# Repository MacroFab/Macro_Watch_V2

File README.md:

***
### Macro_Watch_V2
***
**Low cost, binary watch based off the Silicon Labs EFM8SB10F2G-A-QFN20R MCU for promotional purposes at MacroFab, INC.**

This repository contains all the documentation and instructions needed to build a Macro_Watch. The Macro_Watch is designed to be mounted on an ESD wrist band. It is designed to be programmed with the [Silicon Labs USB Debug Adapter](http://www.silabs.com/products/mcu/Pages/USBDebug.aspx) and the [SiLabs2TC](https://github.com/MacroFab/Macro_Articles/tree/master/SiLabs2TC) board. 

Check the [MacroFab, INC. Engineering Blog](https://macrofab.com/blog/engineering/) for more information.

***
**License Information**

This project is under the [Creative Commons Attribution-ShareAlike 4.0 International License](LICENSE.md). This project is provided with no warranty and should be used at your own risk. 

***
**Board Layout**

***
**Board Schematic**

***
**Completed Macro_Watch V2**

***
**Macro_Watch V2 being programmed**

***
**Directory listing of the repository**

| Directory | Description |
|---|---|
| Hardware | Contains all the hardware files for the Macro_Watch. Designed with Eagle V6.0+. | 
| Software | Has all the firmware that needs to be loaded onto the Macro_Watch. Written in C for Simplicity Studio. |

***
**Credits**

Designed by:   
Parker Dillmann  

Software by:   
Parker Dillmann  

***

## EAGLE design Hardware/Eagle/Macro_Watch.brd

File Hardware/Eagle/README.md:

###Macro_Watch Hardware
***
**Low cost, binary watch based off the Silicon Labs EFM8SB10F2G-A-QFN20R MCU for promotional purposes at MacroFab, INC.**

***

***

***

Files are for Eagle V6.0+. Gerber files can be found in the camfiles directory. See main directory for licensing.

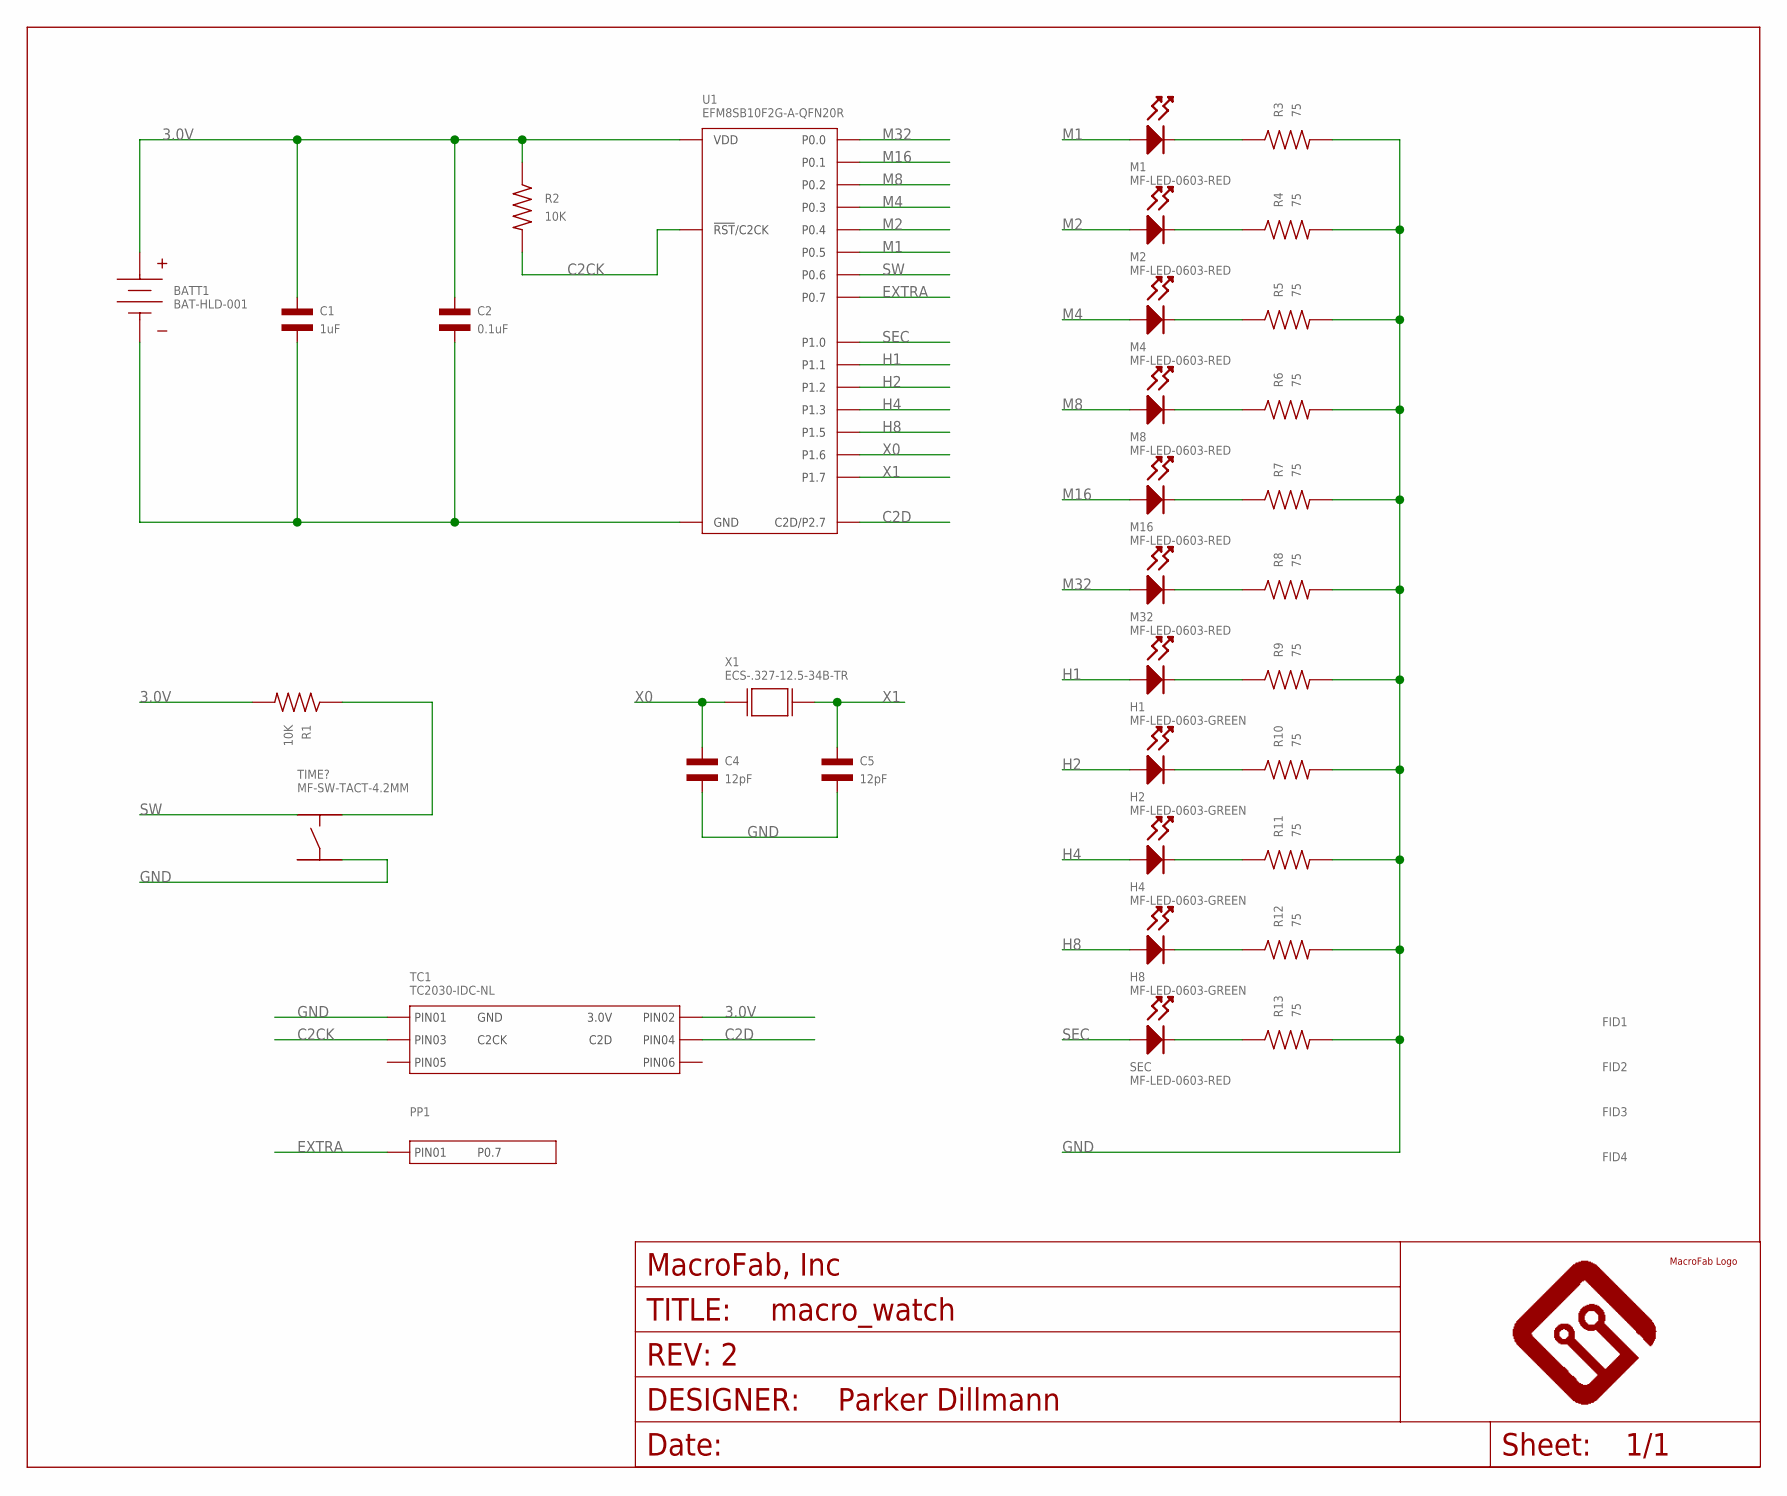
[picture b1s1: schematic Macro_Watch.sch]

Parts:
BATT1: BAT-HLD-001
C1: 1uF; C0402; MPN MF-CAP-0402-1uF
C2: 0.1uF; C0402; MPN MF-CAP-0402-0.1uF
C4, C5: 12pF; C0402; MPN 500R07S120KV4T
FID1, FID2, FID3, FID4: FIDUCIAL_0.5MM
FRAME1: MF_FRAMEDEFAULT; MF_FRAME_DEFAULT
H1, H2, H4, H8: MF-LED-0603-GREEN; LED0603
M1, M2, M4, M8, M16, M32: MF-LED-0603-RED; LED0603
PP1: POGO_PIN_01X01_70-9150; POGO_PIN_70-9150
R1, R2: 10K; R0402; MPN MF-RES-0402-10K
R3, R4, R5, R6, R7, R8, R9, R10, R11, R12, R13: 75; R0402; MPN MF-RES-0402-75
SEC: MF-LED-0603-RED; LED0603
TC1: TC2030-IDC-NL
TIME?: MF-SW-TACT-4.2MM; TACT4.2MM
U1: EFM8SB10F2G-A-QFN20R; EFM8SB10F(2/4/8)G-A-QFN20; MPN EFM8SB10F2G-A-QFN20R
U$1: MF_LOGOLOGO_SMALL; MF_LOGO_SMALL
X1: ECS-.327-12.5-34B-TR; ECX-31B_SERIES; MPN ECS-.327-12.5-34B-TR

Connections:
3.0V: BATT1.POS_0 (POS), BATT1.POS_1 (POS), C1.P$1, C2.P$1, R1.P$2, R2.P$1, TC1.P$2 (PIN2), U1.P$4 (VDD)
C2CK: R2.P$2, TC1.P$3 (PIN3), U1.P$5 (!RST!/C2CK)
C2D: TC1.P$4 (PIN4), U1.P$6 (C2D/P2.7)
EXTRA: PP1.P$1, U1.P$15 (P0.7)
GND: BATT1.NEG_0 (NEG), C1.P$2, C2.P$2, C4.P$2, C5.P$2, R3.P$2, R4.P$2, R5.P$2, R6.P$2, R7.P$2, R8.P$2, R9.P$2, R10.P$2, R11.P$2, R12.P$2, R13.P$2, TC1.P$1 (PIN1), TIME?.P$4, U1.P$3 (GND), U1.P$12 (GND), U1.PAD (GND)
H1: H1.ANODE, U1.P$13 (P1.1)
H2: H2.ANODE, U1.P$11 (P1.2)
H4: H4.ANODE, U1.P$10 (P1.3)
H8: H8.ANODE, U1.P$9 (P1.5)
M1: M1.ANODE, U1.P$17 (P0.5)
M2: M2.ANODE, U1.P$18 (P0.4)
M4: M4.ANODE, U1.P$19 (P0.3)
M8: M8.ANODE, U1.P$20 (P0.2)
M16: M16.ANODE, U1.P$1 (P0.1)
M32: M32.ANODE, U1.P$2 (P0.0)
unnamed: R1.P$1, TIME?.P$2
unnamed: M1.CATHODE, R3.P$1
unnamed: M2.CATHODE, R4.P$1
unnamed: M4.CATHODE, R5.P$1
unnamed: M8.CATHODE, R6.P$1
unnamed: M16.CATHODE, R7.P$1
unnamed: M32.CATHODE, R8.P$1
unnamed: H1.CATHODE, R9.P$1
unnamed: H2.CATHODE, R10.P$1
unnamed: H4.CATHODE, R11.P$1
unnamed: H8.CATHODE, R12.P$1
unnamed: R13.P$1, SEC.CATHODE
SEC: SEC.ANODE, U1.P$14 (P1.0)
SW: TIME?.P$1, U1.P$16 (P0.6)
X0: C4.P$1, U1.P$8 (P1.6), X1.P$1 (X0)
X1: C5.P$1, U1.P$7 (P1.7), X1.P$2 (X1)

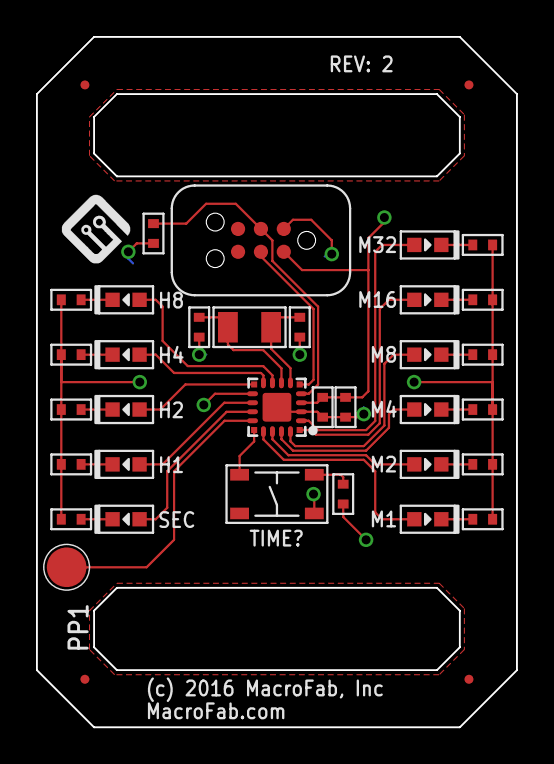
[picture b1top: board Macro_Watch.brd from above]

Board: 2 copper layers, 26.7 x 38.4 mm, 40 parts (1 on the bottom side), 31 nets.

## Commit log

2016-06-27 First push of VS of MacroWatch.
2016-07-21 Code and hardware updated for first production run.
2016-08-08 Updated files to latest Library.
2016-08-10 Adding documentation.
2016-08-10 Fixing syntax for markdown
2017-08-07 Fixed software bug in SiLabs HWConfig

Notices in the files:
parts and their libraries:
MF_Aesthetics: (c) 2016 MacroFab, Inc
